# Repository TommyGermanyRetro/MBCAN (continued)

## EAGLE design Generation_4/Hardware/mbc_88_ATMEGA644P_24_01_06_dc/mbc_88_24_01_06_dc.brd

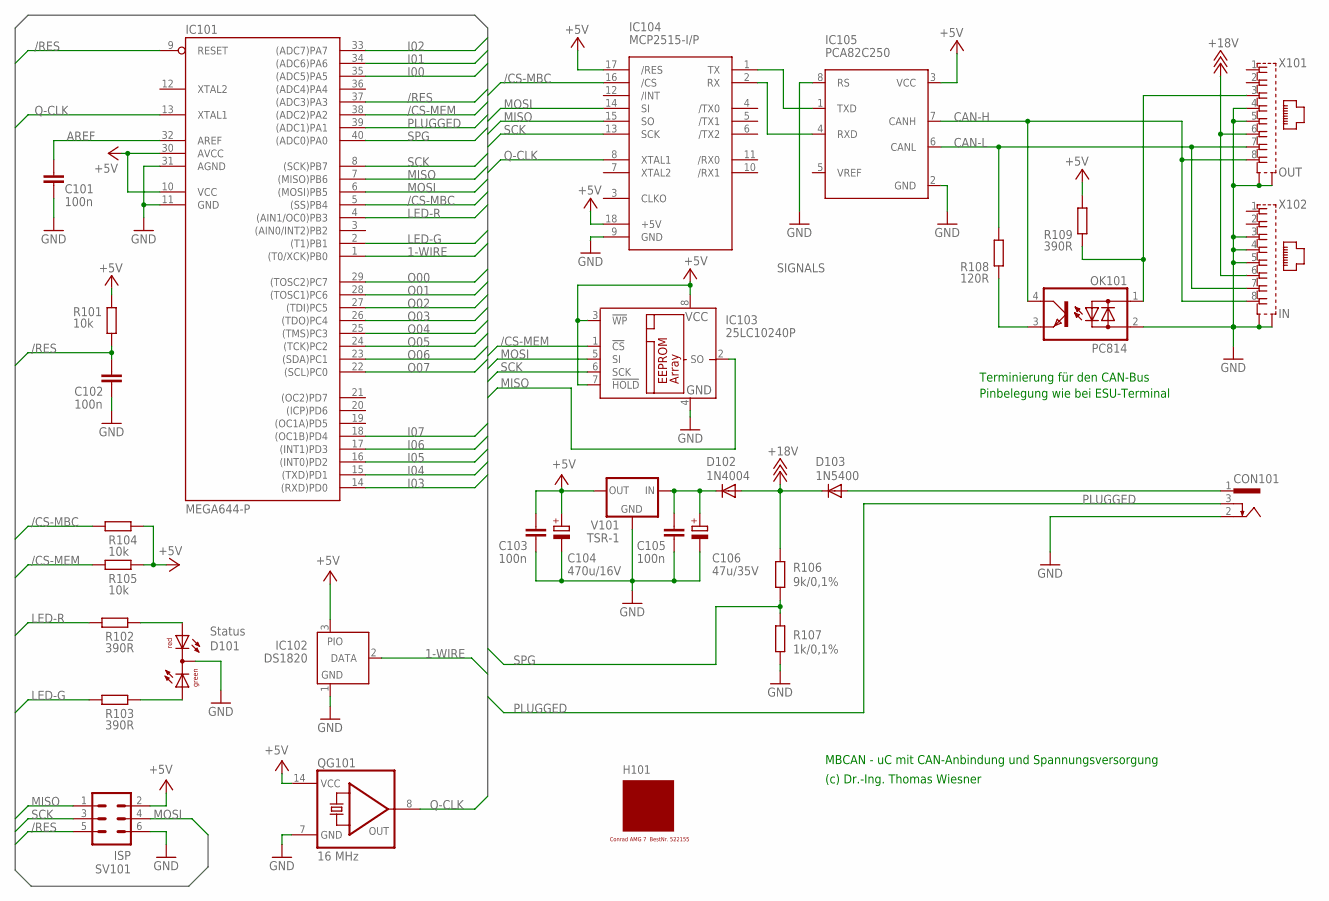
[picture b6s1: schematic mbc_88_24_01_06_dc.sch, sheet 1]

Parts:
C101, C102, C103, C105: 100n; C025-025X050
C104: 470u/16V; E3,5-8
C106: 47u/35V; E2,5-7
CON101: POWER-JACK
D101: Status; DUOLED5MM
D102: 1N4004; DO41-10
D103: 1N5400; DO201-15
H101: MODULGEHÄUSE-AMG-7; MODULGEHÄUSE-1
IC101: MEGA644-P; DIL40
IC102: DS1820; TO92-
IC103: 25LC10240P; DIL8
IC104: MCP2515-I/P; DIL18
IC105: PCA82C250; DIL08
OK101: PC814; DIL04
QG101: 16 MHz; DIL14S
R101, R104, R105: 10k; 0207/10
R102, R103, R109: 390R; 0207/10
R106: 9k/0,1%; 0207/10
R107: 1k/0,1%; 0207/10
R108: 120R; 0207/10
SV101: ISP; ML6
V101: TSR-1; TRACO-TSR-1
X101: OUT; 0446200002
X102: IN; 0446200002

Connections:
1-WIRE: IC101.1 ((T0/XCK)PB0), IC102.2 (DATA)
+5V: C103.1, C104.+, IC101.10 (VCC), IC101.30 (AVCC), IC102.3 (PIO), IC103.3 (!WP), IC103.7 (!HOLD), IC103.8 (VCC), IC104.17 (/RES), IC104.18 (+5V), IC105.3 (VCC), QG101.14 (VCC), R101.2, R104.2, R105.2, R109.2, SV101.2, V101.OUT; also elsewhere on the board
+18V: D102.A, D103.C, R106.1, X101.6, X102.6
/CS-MBC: IC101.5 ((SS)PB4), IC104.16 (/CS), R104.1
/CS-MEM: IC101.38 ((ADC2)PA2), IC103.1 (!CS), R105.1
/RES: C102.1, IC101.9 (RESET), IC101.37 ((ADC3)PA3), R101.1, SV101.5
AREF: C101.1, IC101.32 (AREF)
CAN-H: IC105.7 (CANH), OK101.4 (C), X101.8, X102.8
CAN-L: IC105.6 (CANL), R108.2, X101.7, X102.7
GND: C101.2, C102.2, C103.2, C104.-, C105.2, C106.-, CON101.2, D101.K (C), IC101.11 (GND), IC101.31 (AGND), IC102.1 (GND), IC103.4 (GND), IC104.9 (GND), IC105.2 (GND), IC105.8 (RS), OK101.2 (AC2), QG101.7 (GND), R107.2, SV101.6, V101.GND, X101.4, X101.5, X101.S@1 (S1), X101.S@2 (S2), X102.3, X102.4, X102.5, X102.S@1 (S1), X102.S@2 (S2); also elsewhere on the board
I00: IC101.35 ((ADC5)PA5); also elsewhere on the board
I01: IC101.34 ((ADC6)PA6); also elsewhere on the board
I02: IC101.33 ((ADC7)PA7); also elsewhere on the board
I03: IC101.14 ((RXD)PD0); also elsewhere on the board
I04: IC101.15 ((TXD)PD1); also elsewhere on the board
I05: IC101.16 ((INT0)PD2); also elsewhere on the board
I06: IC101.17 ((INT1)PD3); also elsewhere on the board
I07: IC101.18 ((OC1B)PD4); also elsewhere on the board
LED-G: IC101.2 ((T1)PB1), R103.1
LED-R: IC101.4 ((AIN1/OC0)PB3), R102.1
MISO: IC101.7 ((MISO)PB6), IC103.2 (SO), IC104.15 (SO), SV101.1
MOSI: IC101.6 ((MOSI)PB5), IC103.5 (SI), IC104.14 (SI), SV101.4
unnamed: IC104.1 (TX), IC105.1 (TXD)
unnamed: IC104.2 (RX), IC105.4 (RXD)
unnamed: OK101.1 (AC1), R109.1, X101.3
unnamed: OK101.3 (E), R108.1
unnamed: C105.1, C106.+, D102.C, V101.IN
unnamed: D101.AR, R102.2
unnamed: D101.AG, R103.2
O00: IC101.29 ((TOSC2)PC7); also elsewhere on the board
O01: IC101.28 ((TOSC1)PC6); also elsewhere on the board
O02: IC101.27 ((TDI)PC5); also elsewhere on the board
O03: IC101.26 ((TDO)PC4); also elsewhere on the board
O04: IC101.25 ((TMS)PC3); also elsewhere on the board
O05: IC101.24 ((TCK)PC2); also elsewhere on the board
O06: IC101.23 ((SDA)PC1); also elsewhere on the board
O07: IC101.22 ((SCL)PC0); also elsewhere on the board
PLUGGED: CON101.3, IC101.39 ((ADC1)PA1)
Q-CLK: IC101.13 (XTAL1), IC104.8 (XTAL1), QG101.8 (OUT)
SCK: IC101.8 ((SCK)PB7), IC103.6 (SCK), IC104.13 (SCK), SV101.3
SPG: IC101.40 ((ADC0)PA0), R106.2, R107.1
V-NETZTEIL1: CON101.1, D103.A

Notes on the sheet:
MBCAN - uC mit CAN-Anbindung und Spannungsversorgung
(c) Dr.-Ing. Thomas Wiesner
Terminierung für den CAN-Bus
Pinbelegung wie bei ESU-Terminal

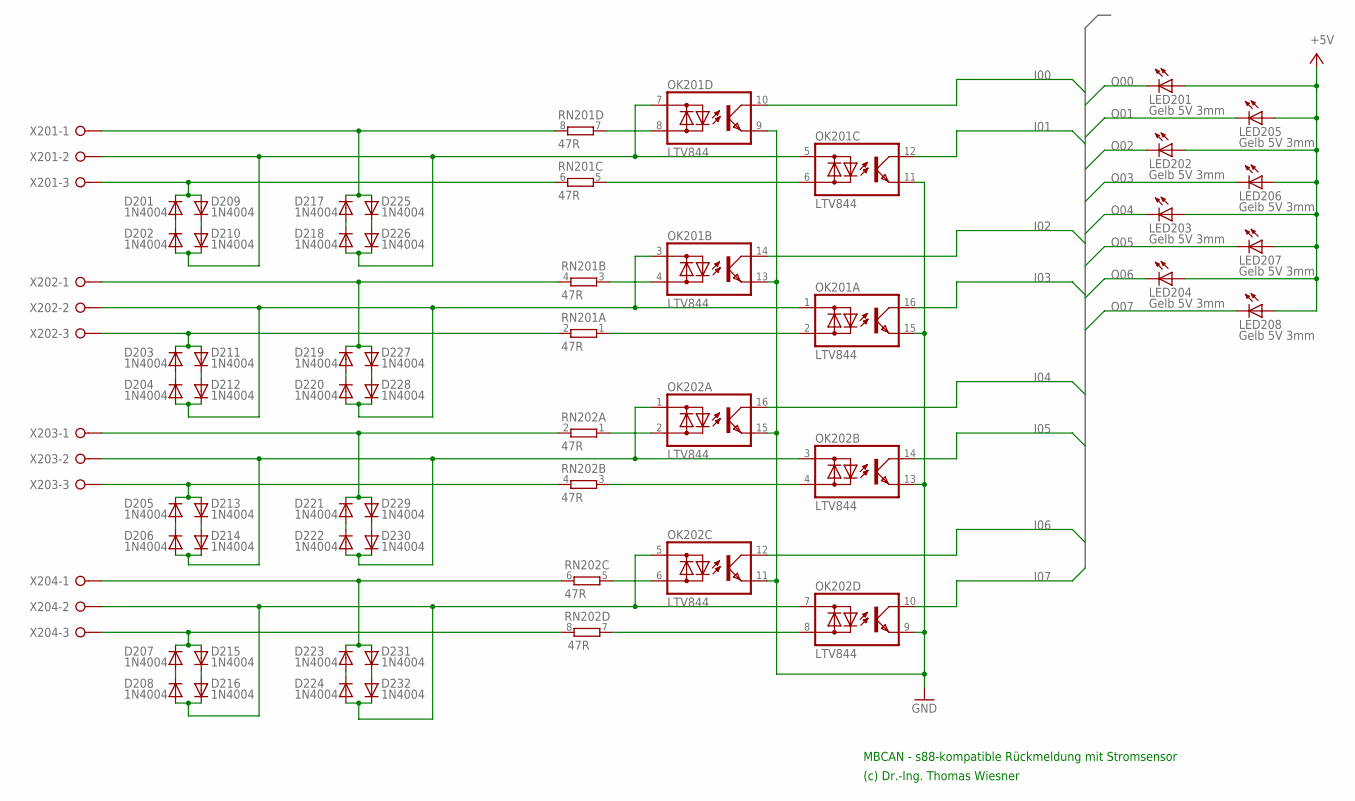
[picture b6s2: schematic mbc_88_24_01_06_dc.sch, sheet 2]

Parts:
D201, D202, D203, D204, D205, D206, D207, D208, D209, D210, D211, D212, D213, D214, D215, D216, D217, D218, D219, D220, D221, D222, D223, D224, D225, D226, D227, D228, D229, D230, D231, D232: 1N4004; DO41-10
LED201, LED202, LED203, LED204, LED205, LED206, LED207, LED208: Gelb 5V 3mm; LED3MM
OK201, OK202: LTV844; DIL16
RN201, RN202: 47R; SIL8
X201, X202, X203, X204: W237-03P; W237-133

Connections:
+5V: LED201.A, LED202.A, LED203.A, LED204.A, LED205.A, LED206.A, LED207.A, LED208.A; also elsewhere on the board
GND: OK201.9 (E), OK201.11 (E), OK201.13 (E), OK201.15 (E), OK202.9 (E), OK202.11 (E), OK202.13 (E), OK202.15 (E); also elsewhere on the board
I00: OK201.10 (C); also elsewhere on the board
I01: OK201.12 (C); also elsewhere on the board
I02: OK201.14 (C); also elsewhere on the board
I03: OK201.16 (C); also elsewhere on the board
I04: OK202.16 (C); also elsewhere on the board
I05: OK202.14 (C); also elsewhere on the board
I06: OK202.12 (C); also elsewhere on the board
I07: OK202.10 (C); also elsewhere on the board
unnamed: D201.A, D202.C
unnamed: D201.C, D209.A, RN201.6 (2), X201.3
unnamed: D217.A, D218.C
unnamed: D225.C, D226.A
unnamed: D217.C, D225.A, RN201.8 (2), X201.1
unnamed: D202.A, D210.C, D218.A, D226.C, OK201.5 (AC1), OK201.7 (AC1), X201.2
unnamed: D203.A, D204.C
unnamed: D209.C, D210.A
unnamed: D211.C, D212.A
unnamed: D203.C, D211.A, RN201.2, X202.3
unnamed: D219.A, D220.C
unnamed: D227.C, D228.A
unnamed: D219.C, D227.A, RN201.4 (2), X202.1
unnamed: D204.A, D212.C, D220.A, D228.C, OK201.1 (AC1), OK201.3 (AC1), X202.2
unnamed: D205.A, D206.C
unnamed: D213.C, D214.A
unnamed: D205.C, D213.A, RN202.4 (2), X203.3
unnamed: D221.A, D222.C
unnamed: D229.C, D230.A
unnamed: D221.C, D229.A, RN202.2, X203.1
unnamed: OK202.8 (AC2), RN202.7 (1)
unnamed: OK202.6 (AC2), RN202.5 (1)
unnamed: OK202.4 (AC2), RN202.3 (1)
unnamed: OK202.2 (AC2), RN202.1
unnamed: OK201.2 (AC2), RN201.1
unnamed: OK201.4 (AC2), RN201.3 (1)
unnamed: D206.A, D214.C, D222.A, D230.C, OK202.1 (AC1), OK202.3 (AC1), X203.2
unnamed: D207.A, D208.C
unnamed: D215.C, D216.A
unnamed: D207.C, D215.A, RN202.8 (2), X204.3
unnamed: D223.A, D224.C
unnamed: D231.C, D232.A
unnamed: D223.C, D231.A, RN202.6 (2), X204.1
unnamed: D208.A, D216.C, D224.A, D232.C, OK202.5 (AC1), OK202.7 (AC1), X204.2
unnamed: OK201.6 (AC2), RN201.5 (1)
unnamed: OK201.8 (AC2), RN201.7 (1)
O00: LED201.K (C); also elsewhere on the board
O01: LED205.K (C); also elsewhere on the board
O02: LED202.K (C); also elsewhere on the board
O03: LED206.K (C); also elsewhere on the board
O04: LED203.K (C); also elsewhere on the board
O05: LED207.K (C); also elsewhere on the board
O06: LED204.K (C); also elsewhere on the board
O07: LED208.K (C); also elsewhere on the board

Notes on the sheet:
MBCAN - s88-kompatible Rückmeldung mit Stromsensor
(c) Dr.-Ing. Thomas Wiesner

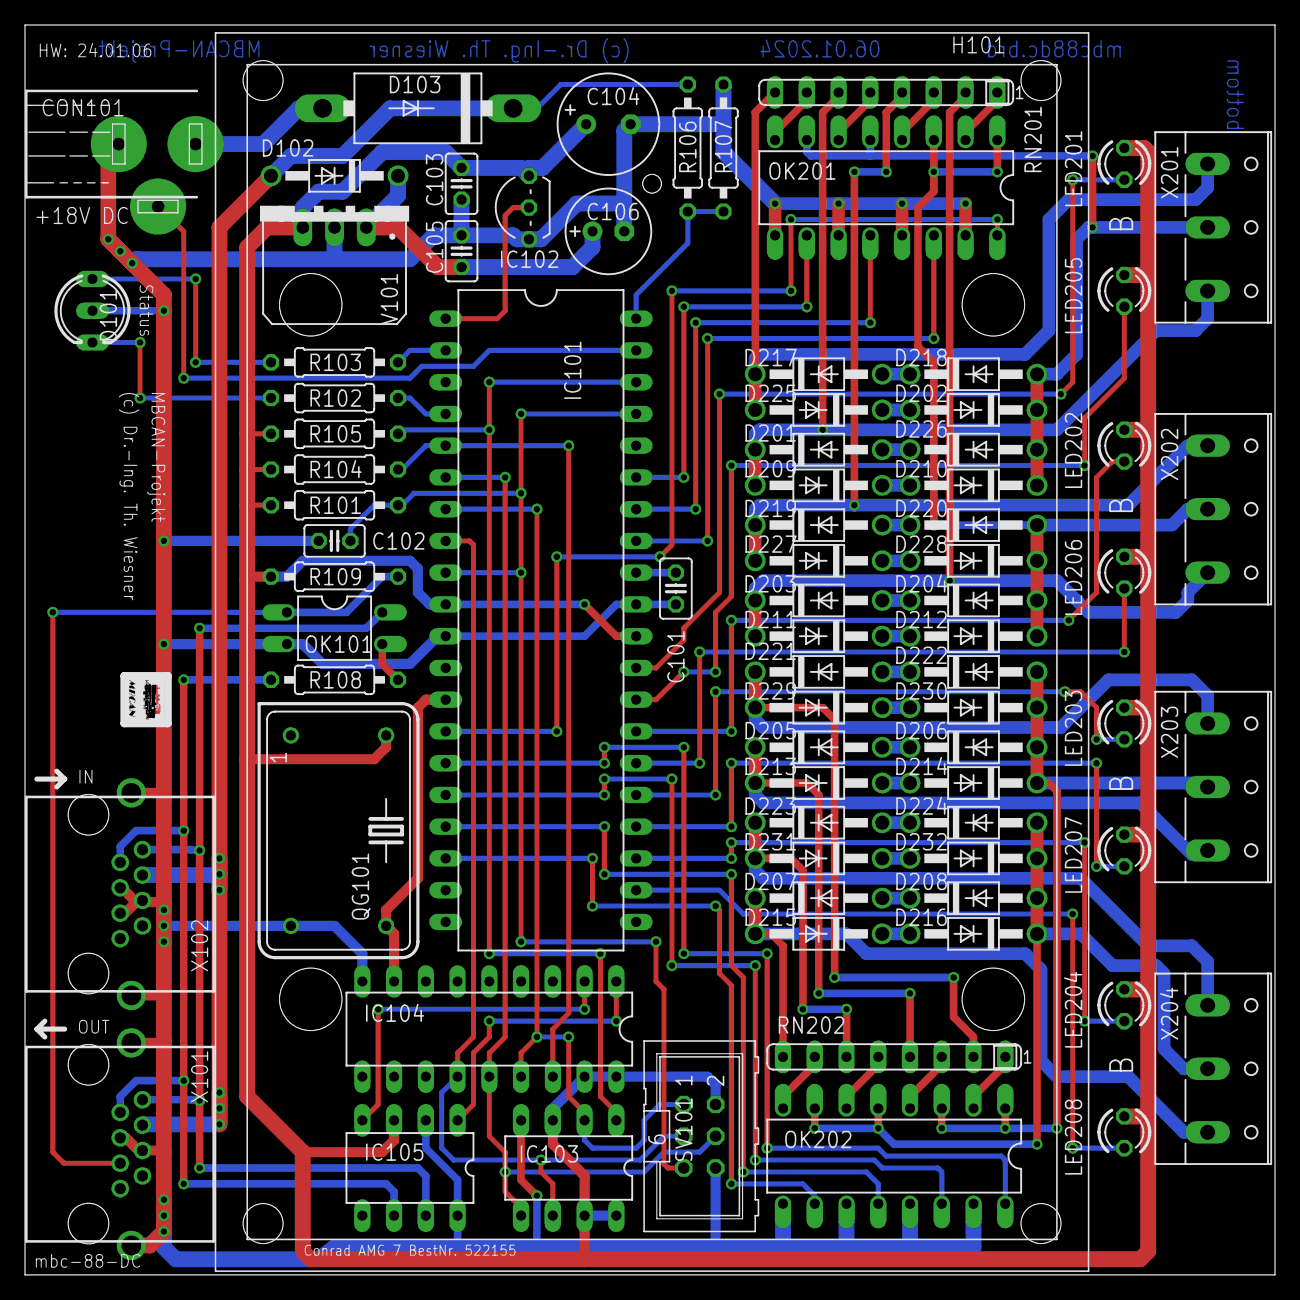
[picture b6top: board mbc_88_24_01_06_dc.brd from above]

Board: 2 copper layers, 100.0 x 100.0 mm, 79 parts (0 on the bottom side), 78 nets.

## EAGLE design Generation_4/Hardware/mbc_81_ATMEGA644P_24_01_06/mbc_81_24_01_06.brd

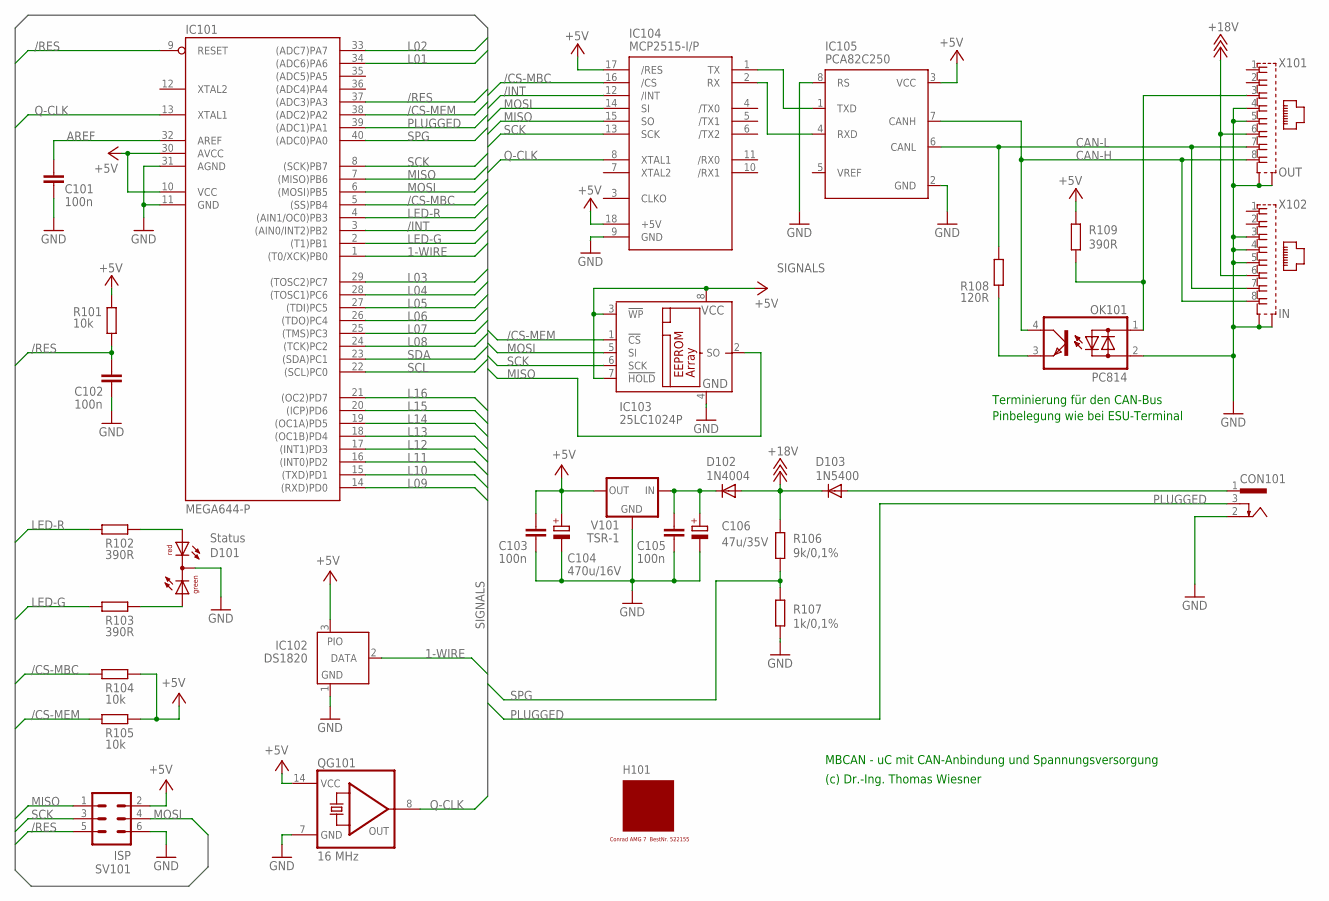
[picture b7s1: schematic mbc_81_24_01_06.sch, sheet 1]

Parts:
C101, C102, C103, C105: 100n; C025-025X050
C104: 470u/16V; E3,5-8
C106: 47u/35V; E2,5-7
CON101: POWER-JACK
D101: Status; DUOLED5MM
D102: 1N4004; DO41-10
D103: 1N5400; DO201-15
H101: MODULGEHÄUSE-AMG-7; MODULGEHÄUSE-1
IC101: MEGA644-P; DIL40
IC102: DS1820; TO92-
IC103: 25LC1024P; DIL8
IC104: MCP2515-I/P; DIL18
IC105: PCA82C250; DIL08
OK101: PC814; DIL04
QG101: 16 MHz; DIL14S
R101, R104, R105: 10k; 0207/10
R102, R103, R109: 390R; 0207/10
R106: 9k/0,1%; 0207/10
R107: 1k/0,1%; 0207/10
R108: 120R; 0207/10
SV101: ISP; ML6
V101: TSR-1; TRACO-TSR-1
X101: OUT; 0446200002
X102: IN; 0446200002

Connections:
1-WIRE: IC101.1 ((T0/XCK)PB0), IC102.2 (DATA)
+5V: C103.1, C104.+, IC101.10 (VCC), IC101.30 (AVCC), IC102.3 (PIO), IC103.3 (!WP), IC103.7 (!HOLD), IC103.8 (VCC), IC104.17 (/RES), IC104.18 (+5V), IC105.3 (VCC), QG101.14 (VCC), R101.2, R104.2, R105.2, R109.1, SV101.2, V101.OUT; also elsewhere on the board
+18V: D102.A, D103.C, R106.1, X101.6, X102.6
/CS-MBC: IC101.5 ((SS)PB4), IC104.16 (/CS), R104.1
/CS-MEM: IC101.38 ((ADC2)PA2), IC103.1 (!CS), R105.1
/INT: IC101.3 ((AIN0/INT2)PB2), IC104.12 (/INT)
/RES: C102.1, IC101.9 (RESET), IC101.37 ((ADC3)PA3), R101.1, SV101.5
AREF: C101.1, IC101.32 (AREF)
CAN-H: IC105.7 (CANH), OK101.4 (C), X101.8, X102.8
CAN-L: IC105.6 (CANL), R108.2, X101.7, X102.7
GND: C101.2, C102.2, C103.2, C104.-, C105.2, C106.-, CON101.2, D101.K (C), IC101.11 (GND), IC101.31 (AGND), IC102.1 (GND), IC103.4 (GND), IC104.9 (GND), IC105.2 (GND), IC105.8 (RS), OK101.2 (AC2), QG101.7 (GND), R107.2, SV101.6, V101.GND, X101.4, X101.5, X101.S@1 (S1), X101.S@2 (S2), X102.3, X102.4, X102.5, X102.S@1 (S1), X102.S@2 (S2); also elsewhere on the board
L01: IC101.34 ((ADC6)PA6); also elsewhere on the board
L02: IC101.33 ((ADC7)PA7); also elsewhere on the board
L03: IC101.29 ((TOSC2)PC7); also elsewhere on the board
L04: IC101.28 ((TOSC1)PC6); also elsewhere on the board
L05: IC101.27 ((TDI)PC5); also elsewhere on the board
L06: IC101.26 ((TDO)PC4); also elsewhere on the board
L07: IC101.25 ((TMS)PC3); also elsewhere on the board
L08: IC101.24 ((TCK)PC2); also elsewhere on the board
L09: IC101.14 ((RXD)PD0); also elsewhere on the board
L10: IC101.15 ((TXD)PD1); also elsewhere on the board
L11: IC101.16 ((INT0)PD2); also elsewhere on the board
L12: IC101.17 ((INT1)PD3); also elsewhere on the board
L13: IC101.18 ((OC1B)PD4); also elsewhere on the board
L14: IC101.19 ((OC1A)PD5); also elsewhere on the board
L15: IC101.20 ((ICP)PD6); also elsewhere on the board
L16: IC101.21 ((OC2)PD7); also elsewhere on the board
LED-G: IC101.2 ((T1)PB1), R103.1
LED-R: IC101.4 ((AIN1/OC0)PB3), R102.1
MISO: IC101.7 ((MISO)PB6), IC103.2 (SO), IC104.15 (SO), SV101.1
MOSI: IC101.6 ((MOSI)PB5), IC103.5 (SI), IC104.14 (SI), SV101.4
unnamed: IC104.1 (TX), IC105.1 (TXD)
unnamed: IC104.2 (RX), IC105.4 (RXD)
unnamed: OK101.3 (E), R108.1
unnamed: OK101.1 (AC1), R109.2, X101.3
unnamed: C105.1, C106.+, D102.C, V101.IN
unnamed: D101.AR, R102.2
unnamed: D101.AG, R103.2
PLUGGED: CON101.3, IC101.39 ((ADC1)PA1)
Q-CLK: IC101.13 (XTAL1), IC104.8 (XTAL1), QG101.8 (OUT)
SCK: IC101.8 ((SCK)PB7), IC103.6 (SCK), IC104.13 (SCK), SV101.3
SCL: IC101.22 ((SCL)PC0); also elsewhere on the board
SDA: IC101.23 ((SDA)PC1); also elsewhere on the board
SPG: IC101.40 ((ADC0)PA0), R106.2, R107.1
V-NETZTEIL1: CON101.1, D103.A

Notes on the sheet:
MBCAN - uC mit CAN-Anbindung und Spannungsversorgung
(c) Dr.-Ing. Thomas Wiesner
Terminierung für den CAN-Bus
Pinbelegung wie bei ESU-Terminal

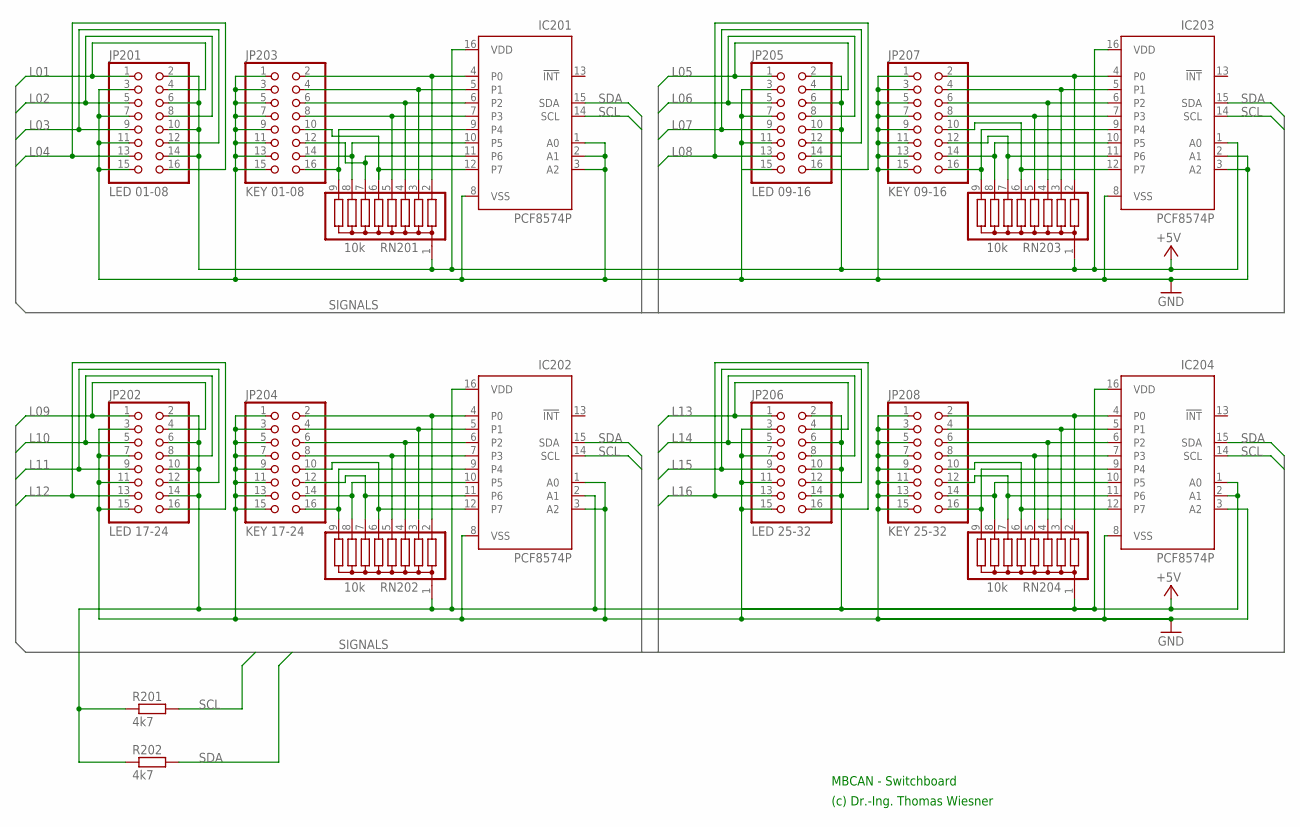
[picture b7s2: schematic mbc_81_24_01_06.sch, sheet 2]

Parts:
IC201, IC202, IC203, IC204: PCF8574P; DIL16
JP201: LED 01-08; 2X08
JP202: LED 17-24; 2X08
JP203: KEY 01-08; 2X08
JP204: KEY 17-24; 2X08
JP205: LED 09-16; 2X08
JP206: LED 25-32; 2X08
JP207: KEY 09-16; 2X08
JP208: KEY 25-32; 2X08
R201, R202: 4k7; 0207/10
RN201, RN202, RN203, RN204: 10k; SIL9

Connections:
+5V: IC201.16 (VDD), IC202.2 (A1), IC202.16 (VDD), IC203.1 (A0), IC203.16 (VDD), IC204.1 (A0), IC204.2 (A1), IC204.16 (VDD), JP201.2, JP201.6, JP201.10, JP201.14, JP202.2, JP202.6, JP202.10, JP202.14, JP205.2, JP205.6, JP205.10, JP205.14, JP206.2, JP206.6, JP206.10, JP206.14, R201.1, R202.1, RN201.1, RN202.1, RN203.1, RN204.1; also elsewhere on the board
GND: IC201.1 (A0), IC201.2 (A1), IC201.3 (A2), IC201.8 (VSS), IC202.1 (A0), IC202.3 (A2), IC202.8 (VSS), IC203.2 (A1), IC203.3 (A2), IC203.8 (VSS), IC204.3 (A2), IC204.8 (VSS), JP201.3, JP201.7, JP201.11, JP201.15, JP202.3, JP202.7, JP202.11, JP202.15, JP203.1, JP203.3, JP203.5, JP203.7, JP203.9, JP203.11, JP203.13, JP203.15, JP204.1, JP204.3, JP204.5, JP204.7, JP204.9, JP204.11, JP204.13, JP204.15, JP205.3, JP205.7, JP205.11, JP205.15, JP206.3, JP206.7, JP206.11, JP206.15, JP207.1, JP207.3, JP207.5, JP207.7, JP207.9, JP207.11, JP207.13, JP207.15, JP208.1, JP208.3, JP208.5, JP208.7, JP208.9, JP208.11, JP208.13, JP208.15; also elsewhere on the board
L01: JP201.1, JP201.4; also elsewhere on the board
L02: JP201.5, JP201.8; also elsewhere on the board
L03: JP201.9, JP201.12; also elsewhere on the board
L04: JP201.13, JP201.16; also elsewhere on the board
L05: JP205.1, JP205.4; also elsewhere on the board
L06: JP205.5, JP205.8; also elsewhere on the board
L07: JP205.9, JP205.12; also elsewhere on the board
L08: JP205.13, JP205.16; also elsewhere on the board
L09: JP202.1, JP202.4; also elsewhere on the board
L10: JP202.5, JP202.8; also elsewhere on the board
L11: JP202.9, JP202.12; also elsewhere on the board
L12: JP202.13, JP202.16; also elsewhere on the board
L13: JP206.1, JP206.4; also elsewhere on the board
L14: JP206.5, JP206.8; also elsewhere on the board
L15: JP206.9, JP206.12; also elsewhere on the board
L16: JP206.13, JP206.16; also elsewhere on the board
unnamed: IC202.4 (P0), JP204.2, RN202.2
unnamed: IC202.5 (P1), JP204.4, RN202.3
unnamed: IC202.6 (P2), JP204.6, RN202.4
unnamed: IC202.7 (P3), JP204.8, RN202.5
unnamed: IC202.12 (P7), JP204.10, RN202.6
unnamed: IC202.11 (P6), JP204.12, RN202.7
unnamed: IC202.10 (P5), JP204.14, RN202.8
unnamed: IC202.9 (P4), JP204.16, RN202.9
unnamed: IC201.4 (P0), JP203.2, RN201.2
unnamed: IC201.5 (P1), JP203.4, RN201.3
unnamed: IC201.6 (P2), JP203.6, RN201.4
unnamed: IC201.7 (P3), JP203.8, RN201.5
unnamed: IC201.9 (P4), JP203.16, RN201.9
unnamed: IC201.10 (P5), JP203.14, RN201.8
unnamed: IC201.11 (P6), JP203.12, RN201.7
unnamed: IC203.4 (P0), JP207.2, RN203.2
unnamed: IC203.5 (P1), JP207.4, RN203.3
unnamed: IC203.6 (P2), JP207.6, RN203.4
unnamed: IC203.7 (P3), JP207.8, RN203.5
unnamed: IC203.12 (P7), JP207.10, RN203.6
unnamed: IC203.11 (P6), JP207.12, RN203.7
unnamed: IC203.10 (P5), JP207.14, RN203.8
unnamed: IC203.9 (P4), JP207.16, RN203.9
unnamed: IC204.4 (P0), JP208.2, RN204.2
unnamed: IC204.5 (P1), JP208.4, RN204.3
unnamed: IC204.6 (P2), JP208.6, RN204.4
unnamed: IC204.7 (P3), JP208.8, RN204.5
unnamed: IC204.12 (P7), JP208.10, RN204.6
unnamed: IC204.11 (P6), JP208.12, RN204.7
unnamed: IC204.10 (P5), JP208.14, RN204.8
unnamed: IC204.9 (P4), JP208.16, RN204.9
unnamed: IC201.12 (P7), JP203.10, RN201.6
SCL: IC201.14 (SCL), IC202.14 (SCL), IC203.14 (SCL), IC204.14 (SCL), R201.2; also elsewhere on the board
SDA: IC201.15 (SDA), IC202.15 (SDA), IC203.15 (SDA), IC204.15 (SDA), R202.2; also elsewhere on the board

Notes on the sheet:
MBCAN - Switchboard
(c) Dr.-Ing. Thomas Wiesner

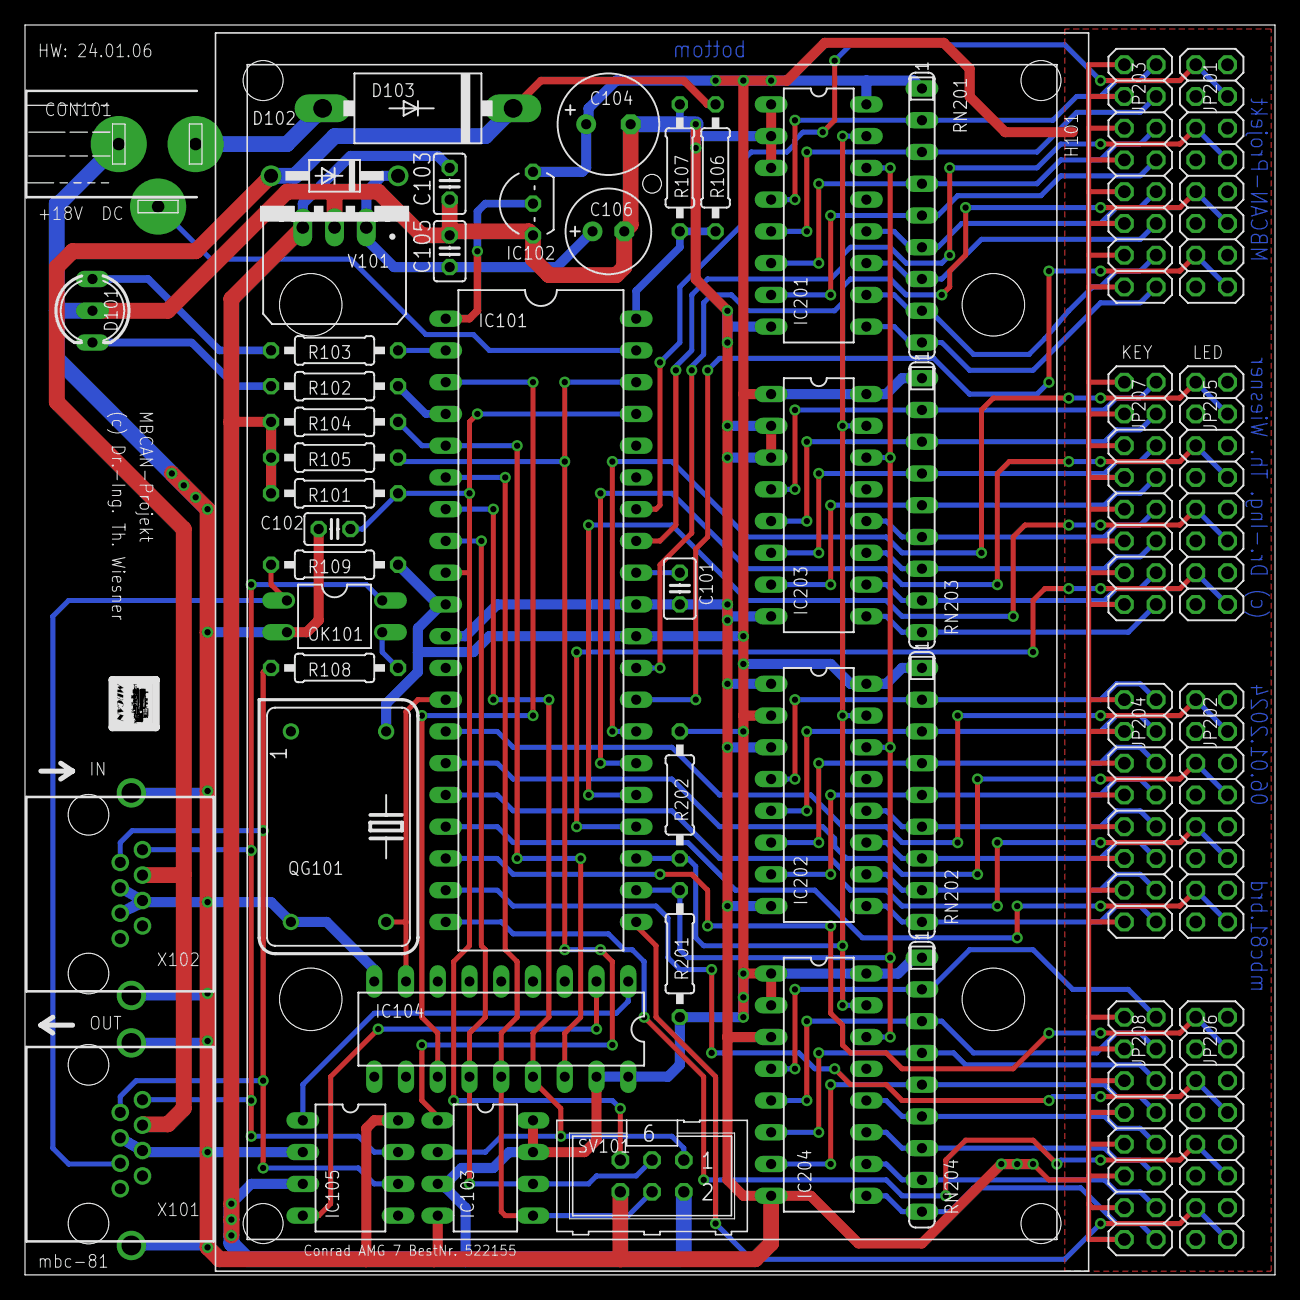
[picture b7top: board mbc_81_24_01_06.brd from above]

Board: 2 copper layers, 100.0 x 100.0 mm, 49 parts (0 on the bottom side), 77 nets.

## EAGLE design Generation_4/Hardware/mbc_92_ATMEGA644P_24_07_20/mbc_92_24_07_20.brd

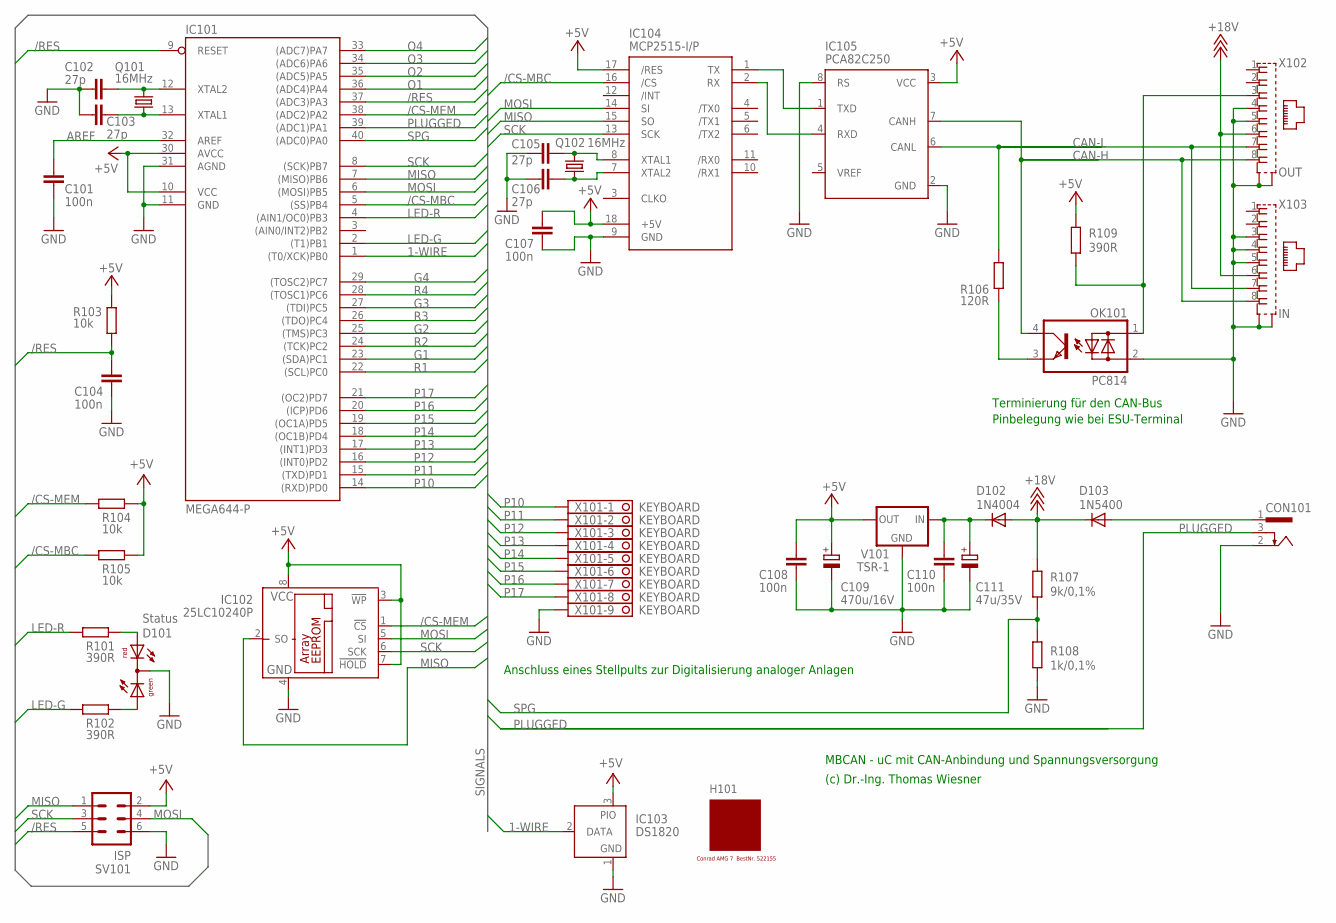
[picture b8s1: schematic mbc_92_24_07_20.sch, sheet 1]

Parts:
C101, C104, C107, C108, C110: 100n; C025-025X050
C102, C103, C105, C106: 27p; C025-025X050
C109: 470u/16V; E3,5-8
C111: 47u/35V; E2,5-7
CON101: POWER-JACK
D101: Status; DUOLED5MM
D102: 1N4004; DO41-10
D103: 1N5400; DO201-15
H101: MODULGEHÄUSE-AMG-7; MODULGEHÄUSE-1
IC101: MEGA644-P; DIL40
IC102: 25LC10240P; DIL8
IC103: DS1820; TO92-
IC104: MCP2515-I/P; DIL18
IC105: PCA82C250; DIL08
OK101: PC814; DIL04
Q101, Q102: 16MHz; HC49U70
R101, R102, R109: 390R; 0207/10
R103, R104, R105: 10k; 0207/10
R106: 120R; 0207/10
R107: 9k/0,1%; 0207/10
R108: 1k/0,1%; 0207/10
SV101: ISP; ML6
V101: TSR-1; TRACO-TSR-1
X101: KEYBOARD; 1751316
X102: OUT; 0446200002
X103: IN; 0446200002

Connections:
1-WIRE: IC101.1 ((T0/XCK)PB0), IC103.2 (DATA)
+5V: C107.1, C108.1, C109.+, IC101.10 (VCC), IC101.30 (AVCC), IC102.3 (!WP), IC102.7 (!HOLD), IC102.8 (VCC), IC103.3 (PIO), IC104.17 (/RES), IC104.18 (+5V), IC105.3 (VCC), R103.2, R104.2, R105.2, R109.1, SV101.2, V101.OUT; also elsewhere on the board
+18V: D102.A, D103.C, R107.1, X102.6, X103.6
/CS-MBC: IC101.5 ((SS)PB4), IC104.16 (/CS), R105.1
/CS-MEM: IC101.38 ((ADC2)PA2), IC102.1 (!CS), R104.1
/RES: C104.1, IC101.9 (RESET), IC101.37 ((ADC3)PA3), R103.1, SV101.5
AREF: C101.1, IC101.32 (AREF)
CAN-H: IC105.7 (CANH), OK101.4 (C), X102.8, X103.8
CAN-L: IC105.6 (CANL), R106.2, X102.7, X103.7
G1: IC101.23 ((SDA)PC1); also elsewhere on the board
G2: IC101.25 ((TMS)PC3); also elsewhere on the board
G3: IC101.27 ((TDI)PC5); also elsewhere on the board
G4: IC101.29 ((TOSC2)PC7); also elsewhere on the board
GND: C101.2, C102.1, C103.1, C104.2, C105.1, C106.1, C107.2, C108.2, C109.-, C110.2, C111.-, CON101.2, D101.K (C), IC101.11 (GND), IC101.31 (AGND), IC102.4 (GND), IC103.1 (GND), IC104.9 (GND), IC105.2 (GND), IC105.8 (RS), OK101.2 (AC2), R108.2, SV101.6, V101.GND, X101.9, X102.4, X102.5, X102.S@1 (S1), X102.S@2 (S2), X103.3, X103.4, X103.5, X103.S@1 (S1), X103.S@2 (S2); also elsewhere on the board
LED-G: IC101.2 ((T1)PB1), R102.1
LED-R: IC101.4 ((AIN1/OC0)PB3), R101.1
MISO: IC101.7 ((MISO)PB6), IC102.2 (SO), IC104.15 (SO), SV101.1
MOSI: IC101.6 ((MOSI)PB5), IC102.5 (SI), IC104.14 (SI), SV101.4
unnamed: IC104.1 (TX), IC105.1 (TXD)
unnamed: IC104.2 (RX), IC105.4 (RXD)
unnamed: OK101.3 (E), R106.1
unnamed: OK101.1 (AC1), R109.2, X102.3
unnamed: C110.1, C111.+, D102.C, V101.IN
unnamed: D101.AR, R101.2
unnamed: D101.AG, R102.2
unnamed: C102.2, IC101.12 (XTAL2), Q101.2
unnamed: C103.2, IC101.13 (XTAL1), Q101.1
unnamed: C105.2, IC104.8 (XTAL1), Q102.2
unnamed: C106.2, IC104.7 (XTAL2), Q102.1
O1: IC101.36 ((ADC4)PA4); also elsewhere on the board
O2: IC101.35 ((ADC5)PA5); also elsewhere on the board
O3: IC101.34 ((ADC6)PA6); also elsewhere on the board
O4: IC101.33 ((ADC7)PA7); also elsewhere on the board
P10: IC101.14 ((RXD)PD0), X101.1
P11: IC101.15 ((TXD)PD1), X101.2
P12: IC101.16 ((INT0)PD2), X101.3
P13: IC101.17 ((INT1)PD3), X101.4
P14: IC101.18 ((OC1B)PD4), X101.5
P15: IC101.19 ((OC1A)PD5), X101.6
P16: IC101.20 ((ICP)PD6), X101.7
P17: IC101.21 ((OC2)PD7), X101.8
PLUGGED: CON101.3, IC101.39 ((ADC1)PA1)
R1: IC101.22 ((SCL)PC0); also elsewhere on the board
R2: IC101.24 ((TCK)PC2); also elsewhere on the board
R3: IC101.26 ((TDO)PC4); also elsewhere on the board
R4: IC101.28 ((TOSC1)PC6); also elsewhere on the board
SCK: IC101.8 ((SCK)PB7), IC102.6 (SCK), IC104.13 (SCK), SV101.3
SPG: IC101.40 ((ADC0)PA0), R107.2, R108.1
V-NETZTEIL1: CON101.1, D103.A

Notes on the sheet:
MBCAN - uC mit CAN-Anbindung und Spannungsversorgung
(c) Dr.-Ing. Thomas Wiesner
Terminierung für den CAN-Bus
Pinbelegung wie bei ESU-Terminal
Anschluss eines Stellpults zur Digitalisierung analoger Anlagen

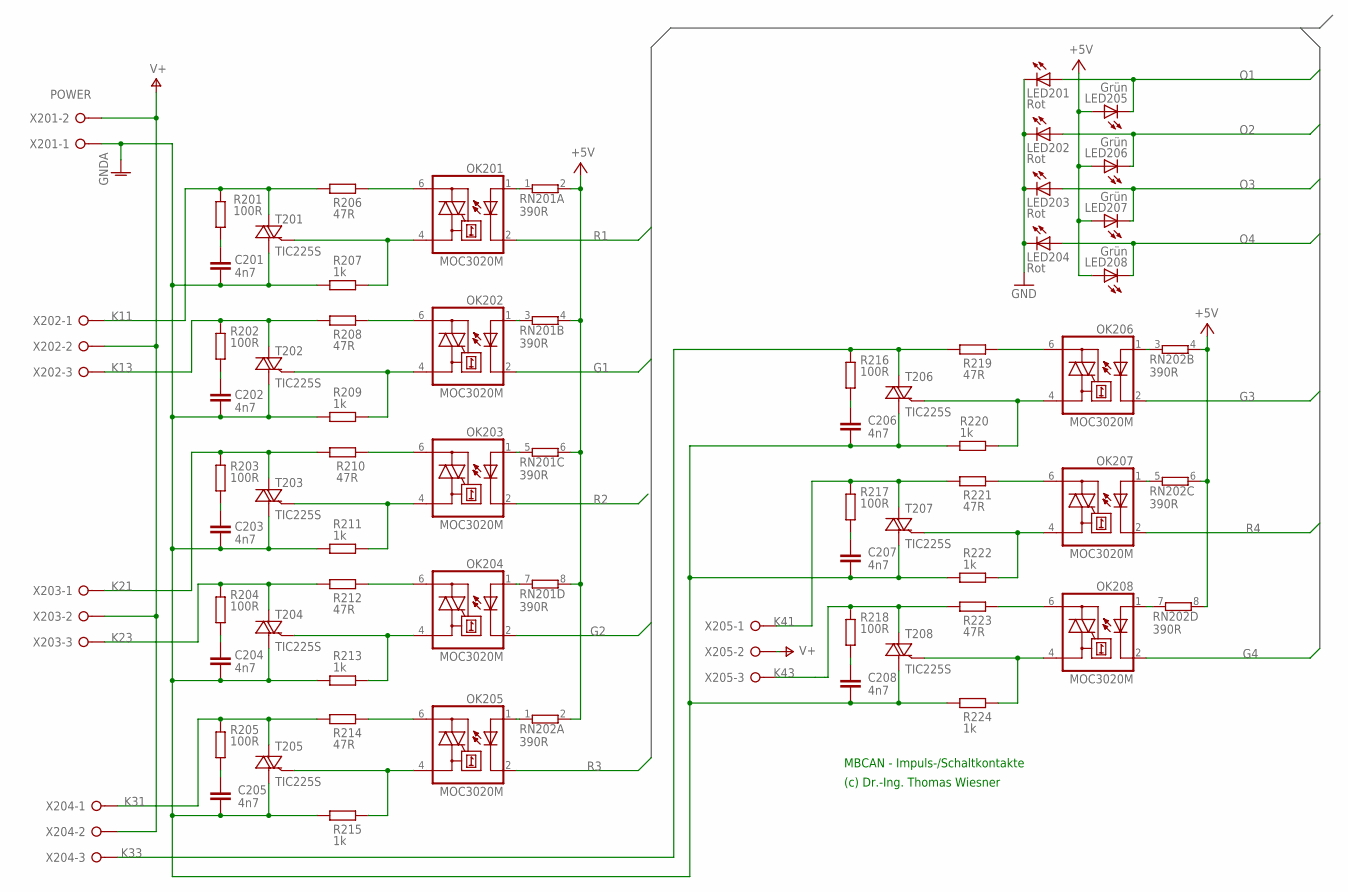
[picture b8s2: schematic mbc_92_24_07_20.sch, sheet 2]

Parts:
C201, C202, C203, C204, C205, C206, C207, C208: 4n7; C025-025X050
LED201, LED202, LED203, LED204: Rot; LED3MM
LED205, LED206, LED207, LED208: Grün; LED3MM
OK201, OK202, OK203, OK204, OK205, OK206, OK207, OK208: MOC3020M; DIL06
R201, R202, R203, R204, R205, R216, R217, R218: 100R; 0207/10
R206, R208, R210, R212, R214, R219, R221, R223: 47R; 0207/10
R207, R209, R211, R213, R215, R220, R222, R224: 1k; 0207/10
RN201, RN202: 390R; SIL8
T201, T202, T203, T204, T205, T206, T207, T208: TIC225S; TO220DS
X201: POWER; W237-132
X202, X203, X204, X205: W237-03P; W237-133

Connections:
+5V: LED205.A, LED206.A, LED207.A, LED208.A, RN201.2, RN201.4 (2), RN201.6 (2), RN201.8 (2), RN202.2, RN202.4 (2), RN202.6 (2), RN202.8 (2); also elsewhere on the board
G1: OK202.2 (C); also elsewhere on the board
G2: OK204.2 (C); also elsewhere on the board
G3: OK206.2 (C); also elsewhere on the board
G4: OK208.2 (C); also elsewhere on the board
GND: LED201.K (C), LED202.K (C), LED203.K (C), LED204.K (C); also elsewhere on the board
GNDA: C201.2, C202.2, C203.2, C204.2, C205.2, C206.2, C207.2, C208.2, R207.2, R209.2, R211.2, R213.2, R215.2, R220.2, R222.2, R224.2, T201.A1, T202.A1, T203.A1, T204.A1, T205.A1, T206.A1, T207.A1, T208.A1, X201.1
K11: R201.1, R206.2, T201.A2, X202.1
K13: R202.1, R208.2, T202.A2, X202.3
K21: R203.1, R210.2, T203.A2, X203.1
K23: R204.1, R212.2, T204.A2, X203.3
K31: R205.1, R214.2, T205.A2, X204.1
K33: R216.1, R219.2, T206.A2, X204.3
K41: R217.1, R221.2, T207.A2, X205.1
K43: R218.1, R223.2, T208.A2, X205.3
unnamed: OK206.1 (A), RN202.3 (1)
unnamed: OK201.1 (A), RN201.1
unnamed: OK206.4 (A1), R220.1, T206.G
unnamed: OK201.4 (A1), R207.1, T201.G
unnamed: OK201.6 (A2), R206.1
unnamed: OK202.1 (A), RN201.3 (1)
unnamed: OK206.6 (A2), R219.1
unnamed: C201.1, R201.2
unnamed: C206.1, R216.2
unnamed: OK202.4 (A1), R209.1, T202.G
unnamed: OK202.6 (A2), R208.1
unnamed: OK207.1 (A), RN202.5 (1)
unnamed: C202.1, R202.2
unnamed: OK203.1 (A), RN201.5 (1)
unnamed: OK207.4 (A1), R222.1, T207.G
unnamed: OK203.4 (A1), R211.1, T203.G
unnamed: OK203.6 (A2), R210.1
unnamed: OK207.6 (A2), R221.1
unnamed: C203.1, R203.2
unnamed: OK204.1 (A), RN201.7 (1)
unnamed: C207.1, R217.2
unnamed: OK204.4 (A1), R213.1, T204.G
unnamed: OK204.6 (A2), R212.1
unnamed: OK208.1 (A), RN202.7 (1)
unnamed: C204.1, R204.2
unnamed: OK205.1 (A), RN202.1
unnamed: OK208.4 (A1), R224.1, T208.G
unnamed: OK205.4 (A1), R215.1, T205.G
unnamed: OK205.6 (A2), R214.1
unnamed: OK208.6 (A2), R223.1
unnamed: C205.1, R205.2
unnamed: C208.1, R218.2
O1: LED201.A, LED205.K (C); also elsewhere on the board
O2: LED202.A, LED206.K (C); also elsewhere on the board
O3: LED203.A, LED207.K (C); also elsewhere on the board
O4: LED204.A, LED208.K (C); also elsewhere on the board
R1: OK201.2 (C); also elsewhere on the board
R2: OK203.2 (C); also elsewhere on the board
R3: OK205.2 (C); also elsewhere on the board
R4: OK207.2 (C); also elsewhere on the board
V+: X201.2, X202.2, X203.2, X204.2, X205.2

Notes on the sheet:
MBCAN - Impuls-/Schaltkontakte
(c) Dr.-Ing. Thomas Wiesner
